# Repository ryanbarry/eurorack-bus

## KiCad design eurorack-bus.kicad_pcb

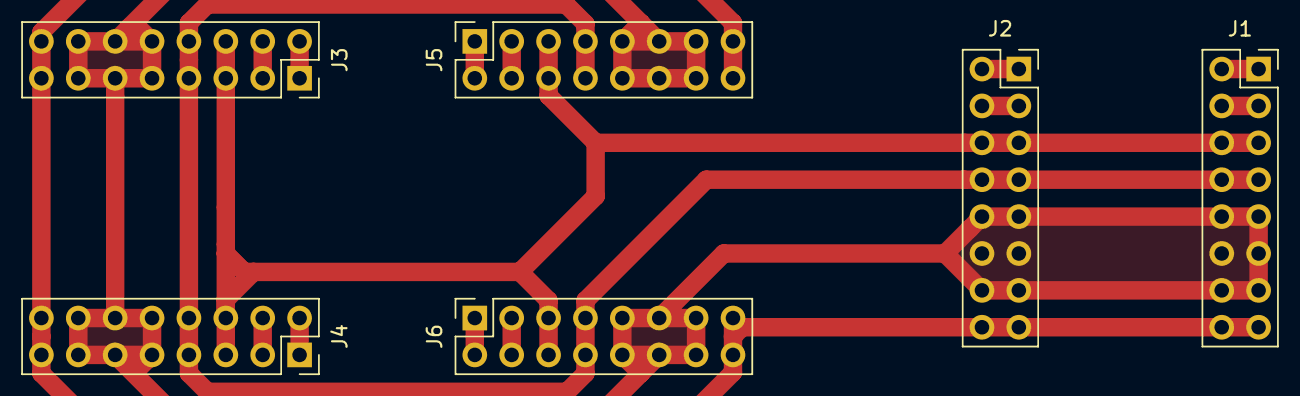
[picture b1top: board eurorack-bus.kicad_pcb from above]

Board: 2 copper layers, 6 parts (0 on the bottom side), 16 nets.

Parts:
J1, J2, J3, J4, J5, J6: Conn_02x08_Odd_Even; PinSocket_2x08_P2.54mm_Vertical

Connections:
unnamed: J1.1, J1.2
unnamed: J1.3, J1.4
unnamed: J1.5, J1.6, J2.5, J2.6, J3.5, J3.6, J4.5, J4.6, J5.5, J5.6, J6.5, J6.6
unnamed: J1.7, J1.8, J2.7, J2.8, J3.7, J3.8, J4.7, J4.8, J5.7, J5.8, J6.7, J6.8
unnamed: J1.9, J1.10, J1.11, J1.12, J1.13, J1.14, J2.9, J2.10, J2.11, J2.12, J2.13, J2.14, J3.9, J3.10, J3.11, J3.12, J3.13, J3.14, J4.9, J4.10, J4.11, J4.12, J4.13, J4.14, J5.9, J5.10, J5.11, J5.12, J5.13, J5.14, J6.9, J6.10, J6.11, J6.12, J6.13, J6.14
unnamed: J1.15, J1.16, J2.15, J2.16, J3.15, J3.16, J4.15, J4.16, J5.15, J5.16, J6.15, J6.16
unnamed: J2.1, J2.2
unnamed: J2.3, J2.4
unnamed: J3.1, J3.2
unnamed: J3.3, J3.4
unnamed: J4.1, J4.2
unnamed: J4.3, J4.4
unnamed: J5.1, J5.2
unnamed: J5.3, J5.4
unnamed: J6.1, J6.2
unnamed: J6.3, J6.4

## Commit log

2019-04-25 basic power bus for 2x4 pcb
2019-04-25 readd conn J2, rm 5v/cv/gt tracks, route
2019-04-25 space things out a little further
2019-05-05 fixup a few traces that should be connected
2019-05-05 add traces for 5v line throughout
2019-06-01 more tweaks to traces
2019-06-01 do the plotting
